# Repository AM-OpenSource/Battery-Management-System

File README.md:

Battery Management System
-------------------------

This project provides software for monitoring, control and charging of batteries
for a solar powered installation.

The motivation to build this arose from the poor performance, lack of
adequate control, lack of configuration for different battery types, and poor
user interface of commercially available BMS, at least for those reasonably
priced.

The system allows for up to three batteries to be managed separately. This
ensures that failed batteries may be isolated without adversely affecting the
other batteries, as could happen if batteries were connected in parallel. Also
note that if batteries were connected in parallel, the same type and age of
battery must be used, which would necessitate changing all batteries if one were
to fail.

The system also allows for up to two loads so that critical low current loads
may be kept running after high current loads are disconnected in the event
that all batteries fall to critically low charge levels.

The system uses several methods of tracking the State of Charge of each battery,
This is a notoriously difficult parameter to estimate. In a system with three
batteries one may be isolated long enough to allow the terminal voltage to
settle to a level that will allow SoC to be computed accurately.

In the long term it is intended to allow a variety of configurations for
charging and monitoring of batteries:

1. The common three phase charger is provided using PWM to reduce the voltage
   in the absorption phase. In float phase the charger is disconnected until the
   terminal voltage drops to a threshold value. Equalization is not provided.

2. An algorithm based on Interrupted Charge Control (ICC) is also provided to
   place batteries in rest when they have reached the gassing voltage and there
   are other batteries to be charged. This has advantages of:
   (a) better utilization of the charger among the batteries,
   (b) low EMI,
   (c) reduced gas generation.

A wide range of state information is stored on a removable memory, and also
transmitted over a serial link to allow a GUI to display the state accurately
and in detail.

A GUI is provided to allow control and observation of operations. The GUI has
been provided also on a BeagleBone Black card with a LCD touchscreen. This
is suitable for wall installation and draws very low power. For wireless
communications, XBees placed in point-point AT serial mode were successful.

Each of the six interfaces has a hardware overcurrent circuit breaker and low
voltage detector, as well as providing current and voltage measurements.

A central controller based on STM32F103 controls all interfaces and the MOSFET
switches directly. Hardware signals for overcurrent and low voltage are applied
directly to the MOSFET switches for rapid disconnect.

A data processing program is also provided to generate reports of various types
from the recorded performance data.

More information is available on [Jiggerjuice](http://www.jiggerjuice.info/electronics/projects/solarbms/solarbms-overview.html).

(c) K. Sarkies 12/09/2015

TODO

1. Improvement of MOSFET switch drivers to reduce EMI at higher rates.
2. MPPT regulator for the panel.
3. Some minor system issues:
* File date error
* Communications hang when errored messages sent.

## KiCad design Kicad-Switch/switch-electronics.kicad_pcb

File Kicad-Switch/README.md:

Battery Management System Switch
--------------------------------

Version 2 of the PCB for the MOSFET switch matrix using SMD components.

Digital circuitry ensures that no two batteries are connected together, which
could cause damage if the state of charge between the batteries differs
significantly.

A diode matrix is used to provide power for the electronics. It ensures that
power is taken from the loads, or from the batteries if the loads are not
connected. This enables the firmware to keep track of the current drawn by
the local electronics.

The MOSFETs are driven by BJT PNP-NPN totem pole drivers. Three [Ideal Diodes](http://www.jiggerjuice.info/electronics/projects/power/ideal-diode.html) 
are also provided in the load circuits to prevent current flowing back to a
battery when a stronger battery is connected to a load. These circuits ensure
that additional voltage drops are kept small. The panel circuit will also
experience such a flow-back in circumstances when the panel voltage is
low. However prevention of this can be done in firmware as there is no value
connecting the panel to a battery if the panel voltage is low.

(c) K. Sarkies 19/01/2018

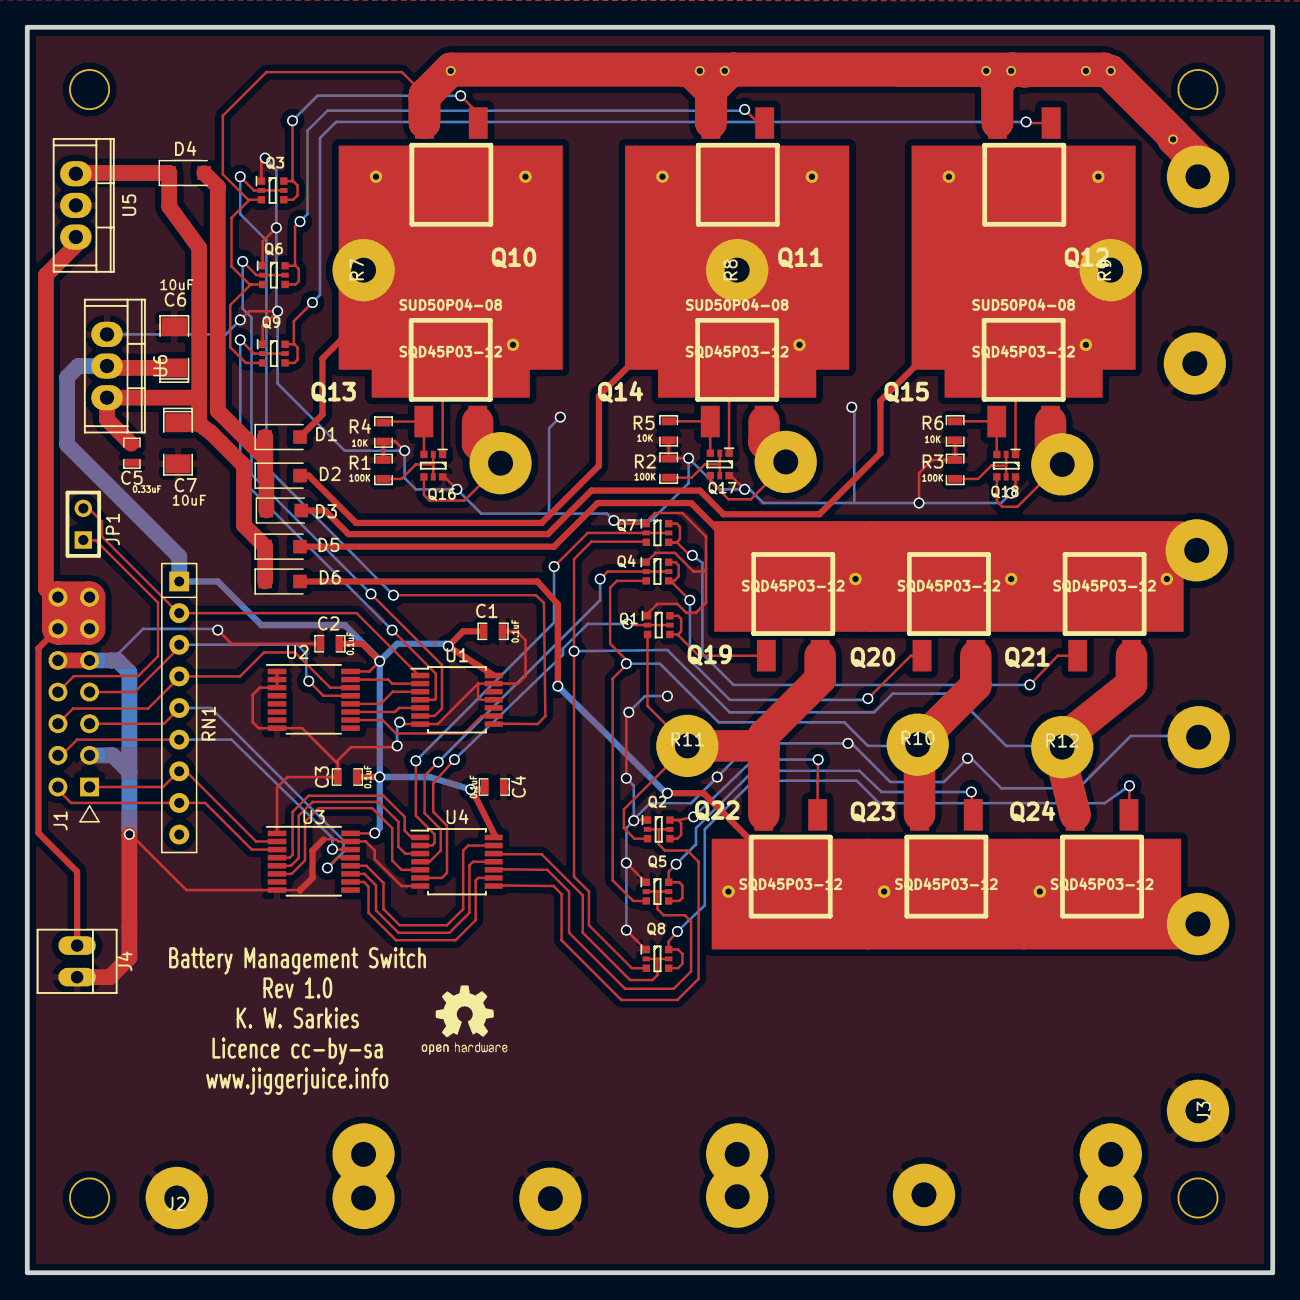
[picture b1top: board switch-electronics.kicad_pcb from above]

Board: 2 copper layers, 100.0 x 100.0 mm, 69 parts (0 on the bottom side), 62 nets.

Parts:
C1, C2, C3, C4: 0.1uF; SM0603_Capa
C5: 0.33uF; SM0603_Capa
C6, C7: 10uF; SM1206POL
D1, D2, D3, D4: 1N4001; D_SOD-123F
D5, D6: 2N5819; D_SOD-123F
J1: Conn_02x07_Odd_Even; header-14-v
J2, J3: Screw_Terminal_01x06; Screw_Terminal_Six
J4: Conn_01x02; PINHEAD1-2
J5, J6, J7, J8, J9, J10, J11, J12: Conn_01x01; THROUGHVIA
JP1: Jumper_NO_Small; SIL-2
Q1, Q2, Q3, Q4, Q5, Q6, Q7, Q8, Q9: BC847BPDW1; SOT-363
Q10, Q11, Q12: SUD50P04-08; TO252-HS-Large
Q13, Q14, Q15, Q19, Q20, Q21, Q22, Q23, Q24: SQD45P03-12; TO252-HS-Small
Q16, Q17, Q18: BC856BDW1; SOT-363
R1, R2, R3: 100K; SM0603_Resistor
R4, R5, R6: 10K; SM0603_Resistor
R7, R8, R9: 0; Link_1
R10: 0; Link_3
R11: 0; Link_2
R12: 0; Link_4
RN1: R_Network08; R_Array_SIP9
U1, U4: 74HC04; TSSOP-14
U2, U3: 74LS139; TSSOP-16
U5: LM7809_TO220; TO-220
U6: LM1086-3.3; TO-220

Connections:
9V: J1.11, J1.12, J1.13, J1.14, J4.1, U5.3
B1: Q1.3, Q2.3, Q19.2, Q22.2, R11.1
B1L1: Q1.4, Q1.6, Q19.1
B1L2: Q2.4, Q2.6, Q22.1
B1M1: Q3.4, Q3.6, Q10.1
B2: Q4.3, Q5.3, Q20.2, Q23.2, R10.1
B2L1: Q4.4, Q4.6, Q20.1
B2L2: Q5.4, Q5.6, Q23.1
B2M1: Q6.4, Q6.6, Q11.1
B3: Q7.3, Q8.3, Q21.2, Q24.2, R12.1
B3L1: Q7.4, Q7.6, Q21.1
B3L2: Q8.4, Q8.6, Q24.1
B3M1: Q9.4, Q9.6, Q12.1
GND: C1.2, C2.2, C3.2, C4.2, C5.2, C6.2, C7.2, J1.3, J1.9, J1.10, J2.1, J2.3, J2.5, J3.1, J3.3, J3.5, J4.2, Q1.1, Q2.1, Q3.1, Q4.1, Q5.1, Q6.1, Q7.1, Q8.1, Q9.1, Q16.6, Q17.6, Q18.6, R1.2, R2.2, R3.2, R4.2, R5.2, R6.2, U1.7, U1.11, U1.13, U2.1, U2.2, U2.3, U2.8, U3.1, U3.8, U3.15, U4.7, U5.2, U6.1
M1: J3.6, J5.1, J6.1, J7.1, J8.1, J9.1, J10.1, J11.1, J12.1, Q3.3, Q6.3, Q9.3, Q10.2, Q11.2, Q12.2
unnamed: C5.1, C7.1, D4.1, D5.1, D6.1, U5.1, U6.3
unnamed: D1.1, D2.1, D3.1, D4.2
unnamed: D1.2, Q10.3, Q13.3, Q16.1, R7.1
unnamed: D2.2, Q11.3, Q14.3, Q17.1, R8.1
unnamed: D3.2, Q12.3, Q15.3, Q18.1, R9.1
unnamed: D5.2, J3.4, Q19.3, Q20.3, Q21.3
unnamed: D6.2, J3.2, Q22.3, Q23.3, Q24.3
unnamed: J1.1, RN1.7, U3.2
unnamed: J1.2, RN1.8, U3.3
unnamed: J1.4, RN1.6, U3.14
unnamed: J1.5, RN1.5, U3.13
unnamed: J1.6, RN1.4, U2.14
unnamed: J1.7, RN1.3, U2.13
unnamed: J1.8, JP1.1
unnamed: J2.2, R7.2
unnamed: J2.4, R8.2
unnamed: J2.6, R9.2
unnamed: JP1.2, RN1.2, U1.1
unnamed: Q1.2, Q1.5, U4.6
unnamed: Q2.2, Q2.5, U4.8
unnamed: Q3.2, Q3.5, U1.8
unnamed: Q4.2, Q4.5, U4.4
unnamed: Q5.2, Q5.5, U4.10
unnamed: Q6.2, Q6.5, U1.6
unnamed: Q7.2, Q7.5, U4.2
unnamed: Q8.2, Q8.5, U4.12
unnamed: Q9.2, Q9.5, U1.4
unnamed: Q13.1, Q16.3, R4.1
unnamed: Q13.2, Q16.4, R11.2
unnamed: Q14.1, Q17.3, R5.1
unnamed: Q14.2, Q17.4, R10.2
unnamed: Q15.1, Q18.3, R6.1
unnamed: Q15.2, Q18.4, R12.2
unnamed: Q16.2, Q16.5, R1.1
unnamed: Q17.2, Q17.5, R2.1
unnamed: Q18.2, Q18.5, R3.1
unnamed: U1.2, U2.15
unnamed: U1.3, U2.12
unnamed: U1.5, U2.11
unnamed: U1.9, U2.10
unnamed: U3.4, U4.1
unnamed: U3.5, U4.3
unnamed: U3.6, U4.5
unnamed: U3.10, U4.9
unnamed: U3.11, U4.11
unnamed: U3.12, U4.13
VCC: C1.1, C2.1, C3.1, C4.1, C6.1, RN1.1, U1.14, U2.16, U3.16, U4.14, U6.2

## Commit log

2015-10-07 GUI bug that limited battery capacity setting in config to 40% minimum. Set back to 0.
2016-03-02 Data Processing incorporate display of temperature
2016-03-02 Firmware minor change to update FreeRTOS version
2016-03-02 GUI Minor change to include QFileInfo library
2016-03-03 Update README to use Markdown hyperlinks
2016-04-04 GUI: correct bug where serial device combobox had no effect.
2016-05-24 Update the firmware readme
2016-07-12 Add states plotting to data processing section.
2016-11-10 Update to latest libopencm3. Update to latest ChaN FatFS Update main file documentation. FreeRTOS updated also but API has not changed and is not reflected here. TODO fix raft of warnings from FreeRT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
2016-11-10 Fix many warning messages from FreeRTOS and some other places. Only warnings now are forced comments.
2016-11-15 Setup of Doxygen documentation structure for firmware Initial documentation of Monitor, Charger, Measurement and Communications tasks.
2016-11-19 Changes to the monitor program to prevent rapid switching back and forth of charger/load allocations when one battery is low or critical. Change to prevent rapid switching of load allocation when cha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
2016-11-19 Firmware: Update doxygen comments to remove all (but one) warnings.
2016-11-19 Rescale GUI configure window calibration tab.
2016-11-19 Update data processing README for more detail on file formats.
2016-11-22 Update to README in data processing and GUI to remind about QT$ usage. Change Qstring.toAscii to Qstring.toLatin1 to avoid later obsolescence.
2016-11-30 Monitor: reduce threshold for turning off charger on low panel voltage. Fix some documentation and inconsistencies. Add debug statements to track down SoC discrepencies. Overall: update to latest lib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
2016-11-30 Update GUI for data processing and add a feature to analyse the combined file for errors and inconsistencies.
2016-11-30 Add a decisionStatus to the monitor when the charger is disconnected by reason of low voltage.
2016-12-02 Firmware: Introduce a millisecond counter and correct the accumulated charge computation in power-system-measurement to use correct time lapse between measurements of currents. Change a few names for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
2016-12-16 Bump version number to 1.03. Modify some documentation. Remove some redundant code.
2016-12-20 Modify BMS monitoring to set SoC to 70% when rest phase is reached. Remove code added earlier, aimed at stopping thrashing in case of a low battery and add hysteresis. Increase time in isolation to 4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
2017-01-04 Change to file operations to replace a processor I/O port number with a macro.
    Bump version number to 1.04
2017-01-09 Correct dumb error in last commit that didn't handle the case where the battery charger was disconnected.
2017-01-09 Minor corrections to comms to null filenames when files are closed. Some small documentation changes.
2017-04-11 firmware: Convert battery state variables to be encapsulated into a battery state struct. This is basically a change in naming only.
2017-04-11 Firmware: modify two battery case by incorporating a new health state of "weak" that causes the charger to be prioritized and all loads to be removed. If the charger is disconnected (usually at night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
2017-04-12 Firmware: Modify remaining cases of more than two batteries to account for weak battery decisions and charger off situations. The charger off is now a boolean variable set when the charger is disconn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
2017-04-16 Firmware: modify monitor logic to unravel and display flow more clearly. Still needs checking. A great deal of repetition would benefit from better structuring.
2017-04-18 Firmware monitor: large scale refactoring of decision block. This is intermediate with the intention of combining two battery and more than two battery cases. Charger: move decision to set SoC to 70%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
2017-04-19 Firmware: merge decision blocks for two batteries and more than two batteries.
2017-04-19 GUI: Change order of locally saved file line endings to satisfy other data processing programs.
2017-04-19 Firmware: Add an additional decision to deallocate the load if the loaded battery becomes low.
2017-04-21 Firmware: remove charger from battery when disabling the charger. Do not restore a battery labelled weak until it is charged to rest phase. This will avoid thrashing in the event of an ailing battery.
2017-04-22 Firmware: Add a check after loads allocated. If the battery under load is low check for a better battery even if it is isolated. Similarly with charger, check for a lower battery even if it is isolat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
2017-04-26 Firmware: Mark battery as weak when voltage falls below a preset voltage (11V). Remove a dynamic test for missing battery as it may erroneously be so labelled by the hardware when the battery charge 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
2017-05-04 GUI: fix problems with parameter recognition and source address/port specification for the TCP version
2017-05-05 GUI: upgraded to QT5. Needs QWT 6.1.3 installed at least.
2017-07-21 Data processing: add feature to extract battery charging behaviour, especially near the float limit. Add feature to extract solar current while batteries are in bulk charging phase.
2017-07-21 Firmware charger: do not allow transfer to float stage to occur until absorption phase current is below the limit for a number (10) of consecutive cycles.
2017-07-21 Firmware monitor: a number of doc and code changes to attempt to correct tendency of the new monitor algorithms to allocate loads to charging battery,
2017-08-01 Firmware: fixed faulty correction factor for Gel/AGM at low SoC
2017-08-11 Data Processing: minor change to labelling of constants.
2017-08-13 firmware: handle missing batteries better to avoid allocations to them.
2017-08-14 data-processing: Fix dumb error made in last mod.
2017-08-14 Firmware: further fixes to monitor to deal with allocation of charger and loads in the case of one battery.
2017-08-26 Firmware Version 1.07. More corrections to handling of missing batteries.
2018-01-25 Switch PCB: first Kicad version complete, not yet verified.
2018-01-26 Complete PCB apart from some points that Kicad doesn't consider to be connected. Reduce size to 100mmx100mm to reduce manufacturing costs.
2018-01-28 Managed to convince Kicad to agree that certain nets were connected to their pads, after adding multiple overlay tracks. Now DRC error free. Adjusted tracks and grounds to ensure that most blank area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
2019-07-21 Replace timer_reset due to change in libopencm3 API Create FreeRTOS task start functions in six modules to move FreeRTOS calls out of the main program into the modules. Change taskDelete calls to use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
2019-07-21 Bump firmware to 1.07b data-processing and gui QT pro files need to add -no-pie to LDFLAGS to allow executables to run Also update QWT to 6.1.3
2019-07-22 Firmware change to ChanFAT 0.13c Update documentation Add extra version information for library support (firmware and GUI) Add some notes in changed files.

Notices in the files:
Kicad-Switch/switch-electronics.kicad_pcb:
Licence cc-by-sa
